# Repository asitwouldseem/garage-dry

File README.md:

# garage-dry
Simple dry contact relay for garage door openers.

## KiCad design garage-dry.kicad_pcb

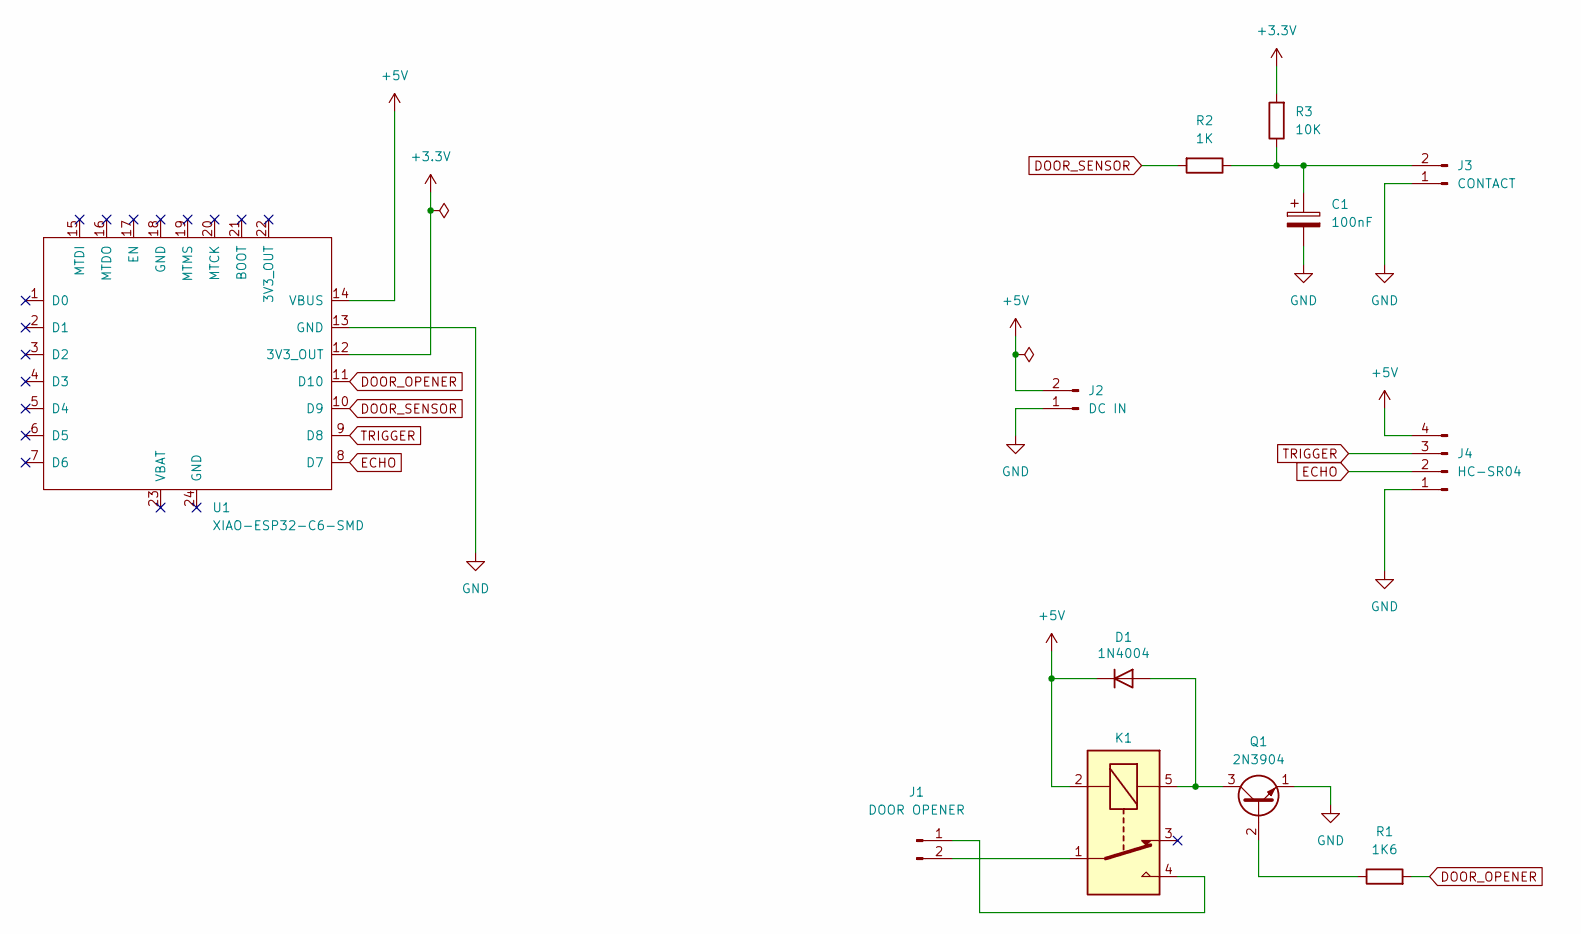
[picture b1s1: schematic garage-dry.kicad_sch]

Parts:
C1: 100nF; C_Disc_D5.0mm_W2.5mm_P5.00mm
D1: 1N4004; D_DO-41_SOD81_P10.16mm_Horizontal
J1: DOOR OPENER; JST_XH_B2B-XH-A_1x02_P2.50mm_Vertical
J2: DC IN; JST_XH_B2B-XH-A_1x02_P2.50mm_Vertical
J3: CONTACT; JST_XH_B2B-XH-A_1x02_P2.50mm_Vertical
J4: HC-SR04; JST_XH_B4B-XH-A_1x04_P2.50mm_Vertical
K1: RELAY6_S55-5V_CUD
Q1: 2N3904; TO-92_Inline
R1: 1K6; R_Axial_DIN0204_L3.6mm_D1.6mm_P7.62mm_Horizontal
R2: 1K; R_Axial_DIN0204_L3.6mm_D1.6mm_P7.62mm_Horizontal
R3: 10K; R_Axial_DIN0204_L3.6mm_D1.6mm_P7.62mm_Horizontal
U1: XIAO-ESP32-C6-SMD; XIAO-ESP32-C6-DIP

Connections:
+3.3V: R3.2, U1.12 (3V3_OUT)
+5V: D1.1 (K), J2.2, J4.4, K1.2, U1.14 (VBUS)
DOOR_OPENER: R1.2, U1.11 (D10)
DOOR_SENSOR: R2.2, U1.10 (D9)
ECHO: J4.2, U1.8 (D7)
GND: C1.2, J2.1, J3.1, J4.1, Q1.1 (E), U1.13 (GND)
unnamed: D1.2 (A), K1.5, Q1.3 (C)
unnamed: J1.1, K1.4
unnamed: J1.2, K1.1
unnamed: C1.1, J3.2, R2.1, R3.1
unnamed: Q1.2 (B), R1.1
TRIGGER: J4.3, U1.9 (D8)

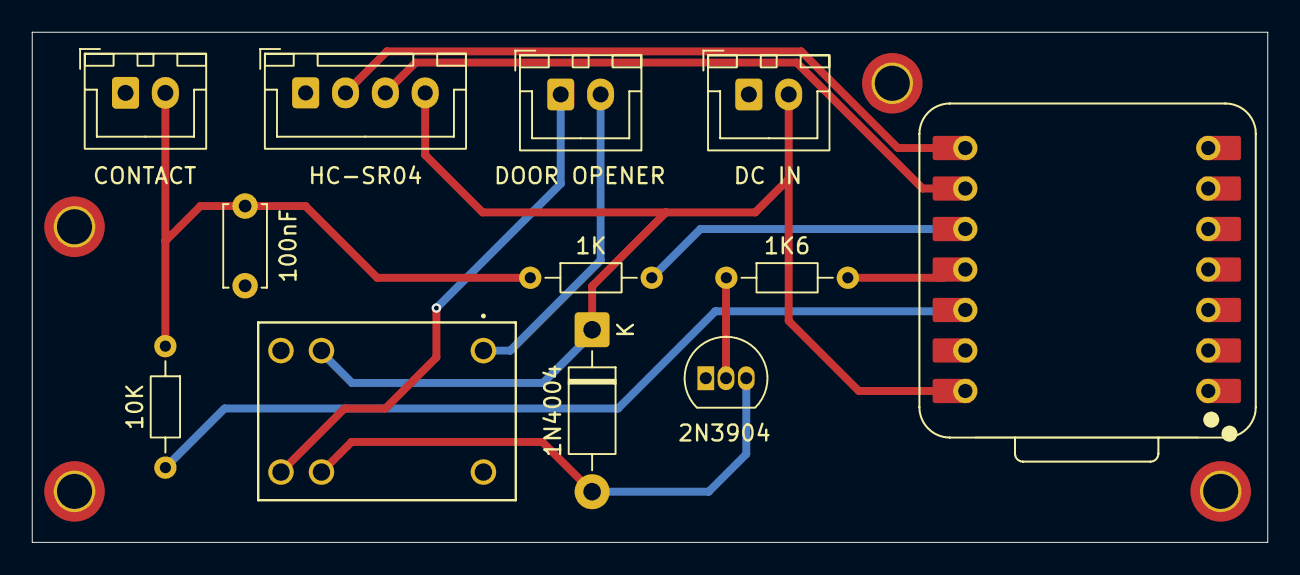
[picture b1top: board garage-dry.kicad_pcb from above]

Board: 2 copper layers, 77.5 x 32.0 mm, 12 parts (0 on the bottom side), 12 nets.
